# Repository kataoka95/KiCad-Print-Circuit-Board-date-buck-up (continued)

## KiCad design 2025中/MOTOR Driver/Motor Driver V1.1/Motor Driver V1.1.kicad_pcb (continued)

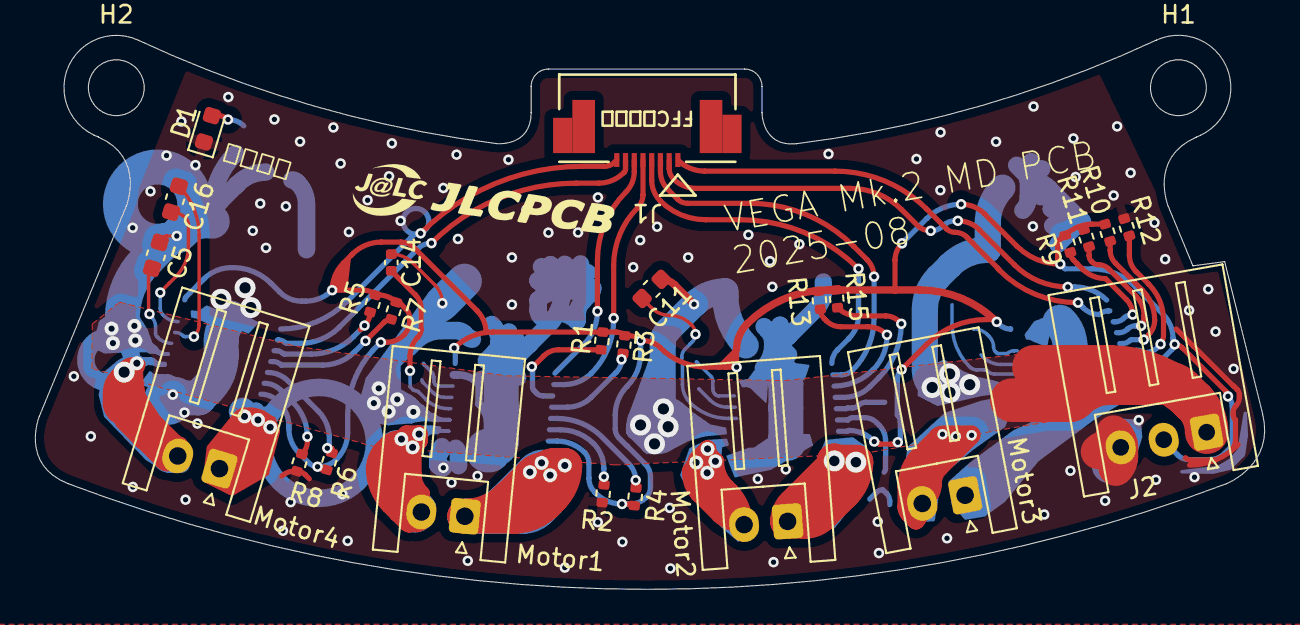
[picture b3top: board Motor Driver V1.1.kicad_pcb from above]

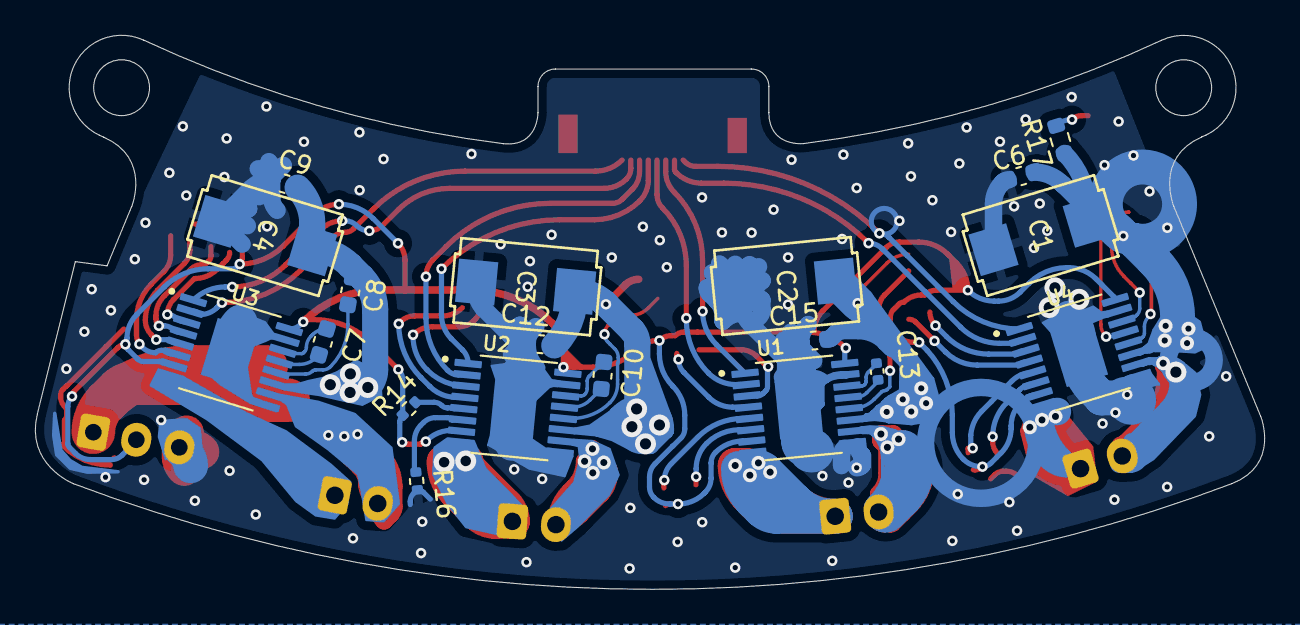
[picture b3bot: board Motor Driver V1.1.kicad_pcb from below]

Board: 2 copper layers, 70.4 x 31.7 mm, 46 parts (19 on the bottom side), 48 nets.

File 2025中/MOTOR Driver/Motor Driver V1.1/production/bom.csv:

Designator,Footprint,Quantity,Value,LCSC Part #
"C1, C2, C3, C4",293D157X9016D2TE3,4,150uF,
"C10, C16, C7",0603,3,22nF,
"C11, C12, C15, C5, C6, C8, C9",0603,7,0.1uF,
C13,0402,1,22nF,
C14,0402,1,0.1uF,
D1,0603,1,LED,
J1,FFC conector 0.5mm Pich,1,Conn_01x08_Pin,
J2,JST_XH_S3B-XH-A_1x03_P2.50mm_Horizontal,1,Conn_01x03_Pin,
"MOTOR1, MOTOR2, MOTOR3, MOTOR4",JST_XH_S2B-XH-A_1x02_P2.50mm_Horizontal,4,Conn_01x02_Pin,
"R1, R10, R11, R13, R14, R15, R3, R4, R5, R6, R7, R9",0402,12,10k,
"R12, R16, R2, R8",0402,4,2.49k,
R17,0603,1,150,
"U1, U2, U3, U4",DRV8874 IC,4,DRV8874PWPR,

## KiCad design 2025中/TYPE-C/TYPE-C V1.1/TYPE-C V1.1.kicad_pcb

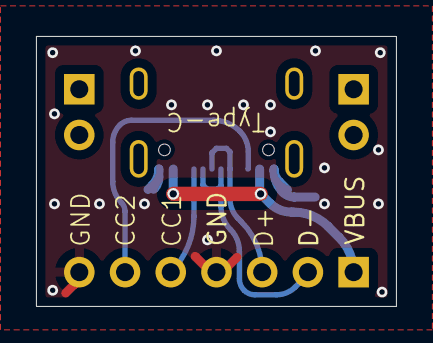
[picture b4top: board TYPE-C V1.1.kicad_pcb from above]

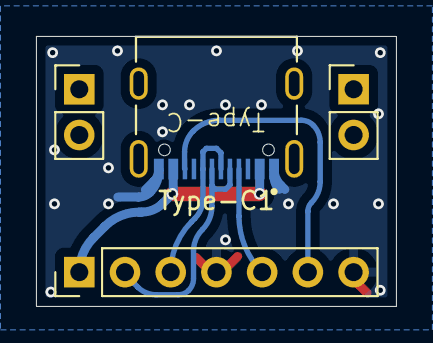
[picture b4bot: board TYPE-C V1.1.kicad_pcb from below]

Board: 2 copper layers, 20.0 x 15.0 mm, 4 parts (4 on the bottom side), 6 nets.

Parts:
J1: Conn_01x07_Pin; PinHeader_1x07_P2.54mm_Vertical
J2, J3: Conn_01x02_Pin; PinHeader_1x02_P2.54mm_Vertical
Type-C1: 5077CR-16SMC2-BK-TR; NELTRON_5077CR-16SMC2-BK-TR

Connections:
CC1: J1.5, Type-C1.A5 (CC1)
CC2: J1.6, Type-C1.B5 (CC2)
D+: J1.3, Type-C1.A6 (DP1), Type-C1.B6 (DP2)
D-: J1.2, Type-C1.A7 (DN1), Type-C1.B7 (DN2)
GND: J1.4, J1.7, Type-C1.A1_B12 (GND), Type-C1.B1_A12 (GND)
VBUS: J1.1, Type-C1.A4_B9 (VBUS), Type-C1.B4_A9 (VBUS)

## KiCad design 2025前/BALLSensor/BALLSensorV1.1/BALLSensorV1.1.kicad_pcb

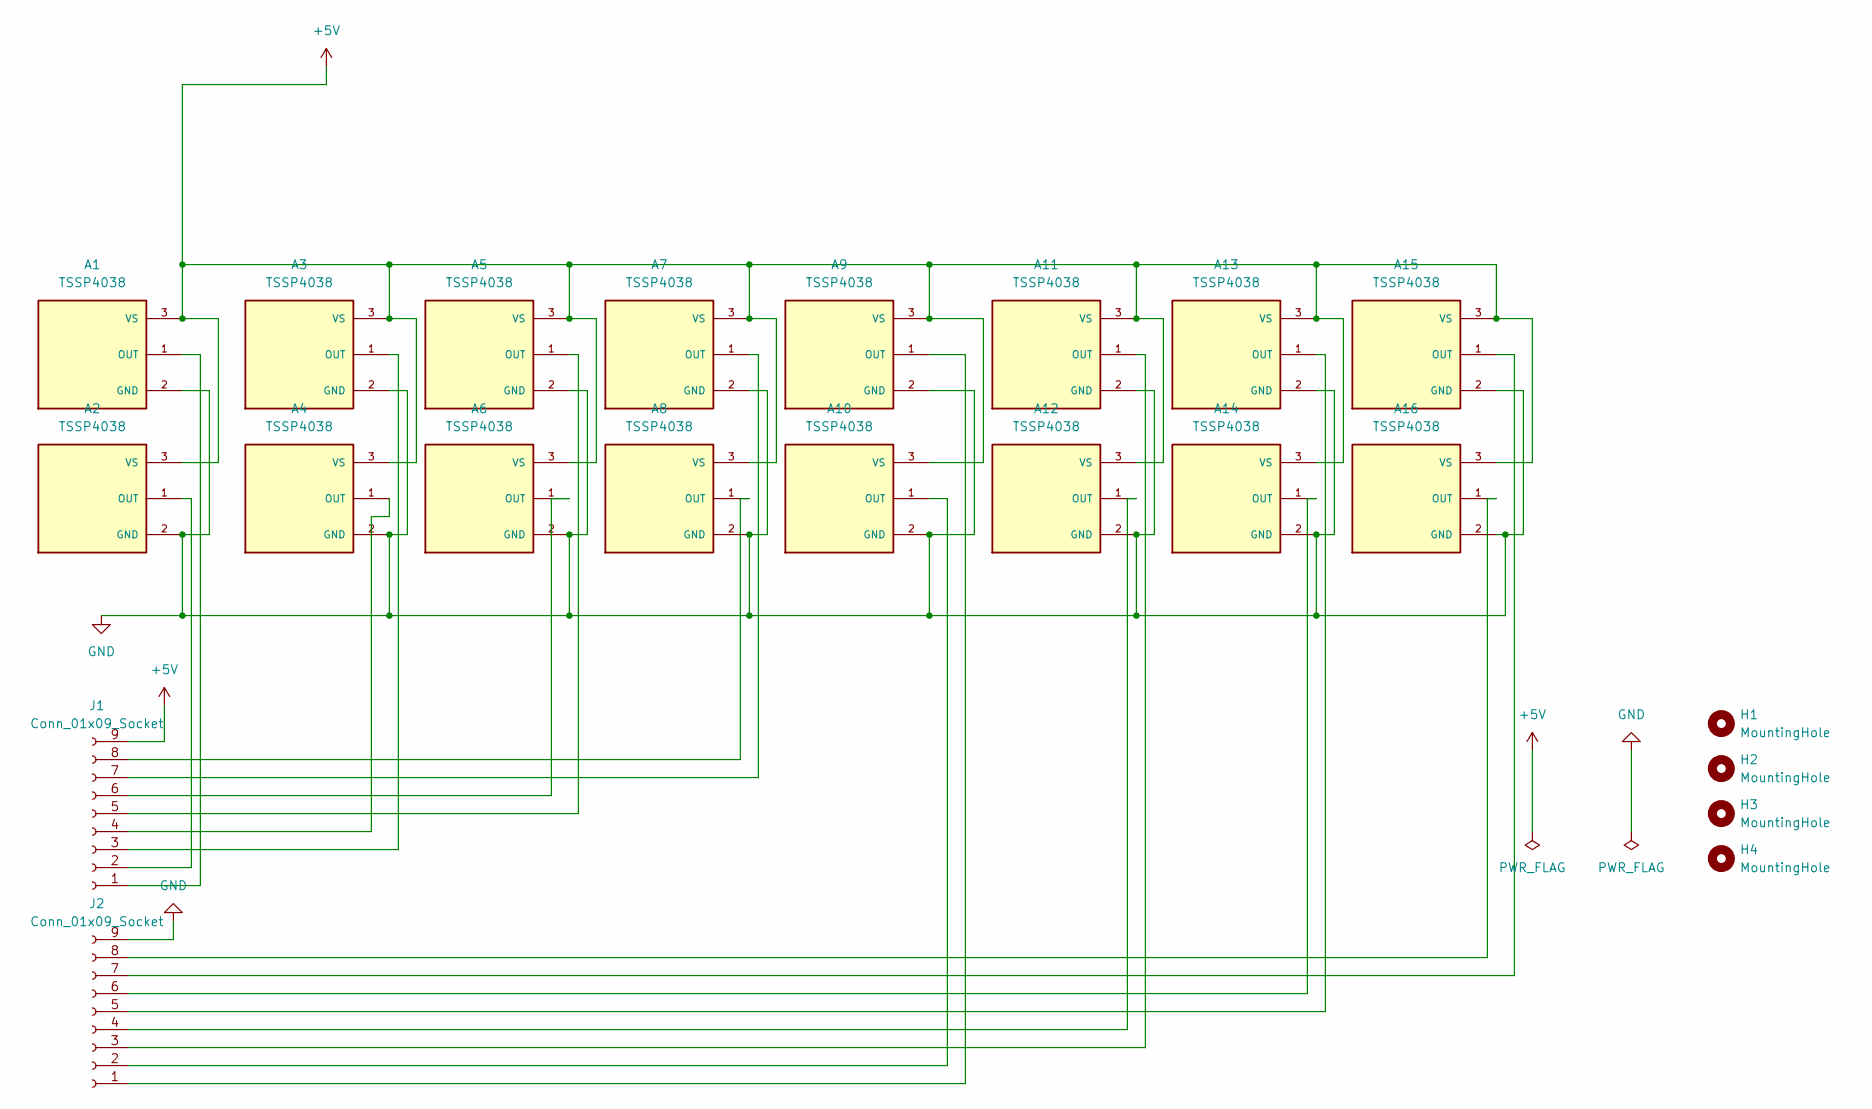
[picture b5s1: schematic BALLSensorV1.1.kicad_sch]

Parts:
A1, A2, A3, A4, A5, A6, A7, A8, A9, A10, A11, A12, A13, A14, A15, A16: TSSP4038; PARTREV 2.3
H1, H2, H3, H4: MountingHole; MountingHole_3.2mm_M3
J1, J2: Conn_01x09_Socket; JST_XH_B9B-XH-A_1x09_P2.50mm_Vertical

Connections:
+5V: A1.3 (VS), A2.3 (VS), A3.3 (VS), A4.3 (VS), A5.3 (VS), A6.3 (VS), A7.3 (VS), A8.3 (VS), A9.3 (VS), A10.3 (VS), A11.3 (VS), A12.3 (VS), A13.3 (VS), A14.3 (VS), A15.3 (VS), A16.3 (VS), J1.9
GND: A1.2 (GND), A2.2 (GND), A3.2 (GND), A4.2 (GND), A5.2 (GND), A6.2 (GND), A7.2 (GND), A8.2 (GND), A9.2 (GND), A10.2 (GND), A11.2 (GND), A12.2 (GND), A13.2 (GND), A14.2 (GND), A15.2 (GND), A16.2 (GND), J2.9
unnamed: A1.1 (OUT), J1.1
unnamed: A2.1 (OUT), J1.2
unnamed: A3.1 (OUT), J1.3
unnamed: A4.1 (OUT), J1.4
unnamed: A5.1 (OUT), J1.5
unnamed: A6.1 (OUT), J1.6
unnamed: A7.1 (OUT), J1.7
unnamed: A8.1 (OUT), J1.8
unnamed: A9.1 (OUT), J2.1
unnamed: A10.1 (OUT), J2.2
unnamed: A11.1 (OUT), J2.3
unnamed: A12.1 (OUT), J2.4
unnamed: A13.1 (OUT), J2.5
unnamed: A14.1 (OUT), J2.6
unnamed: A15.1 (OUT), J2.7
unnamed: A16.1 (OUT), J2.8

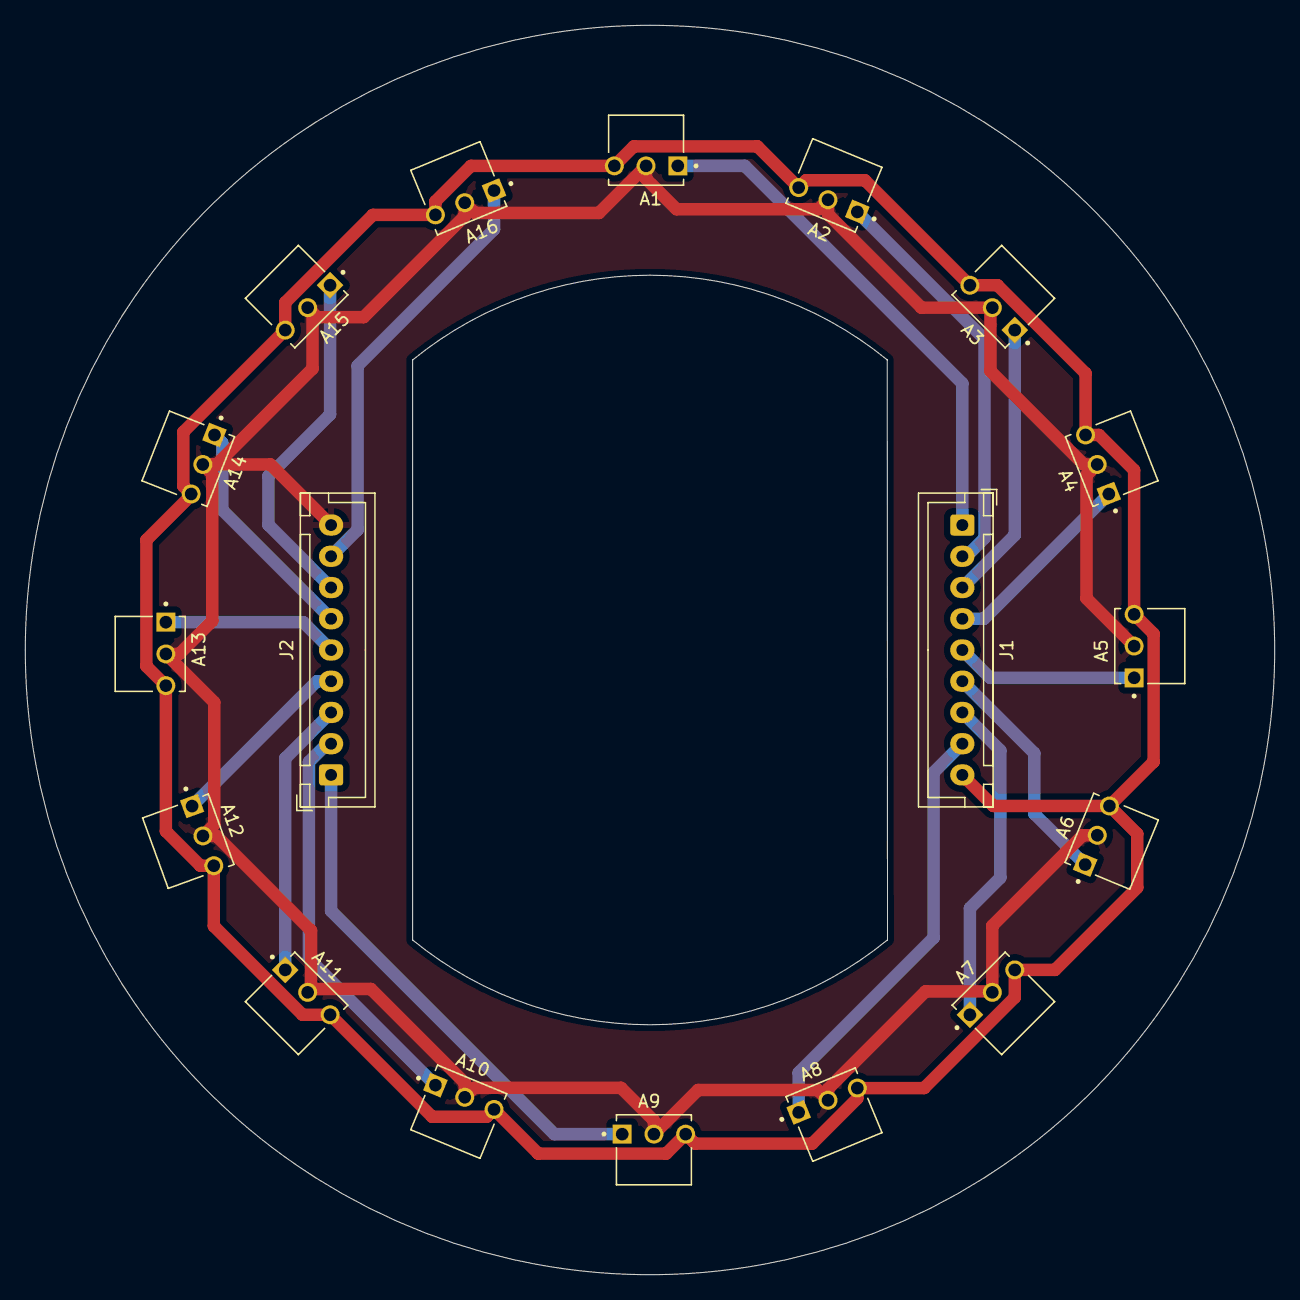
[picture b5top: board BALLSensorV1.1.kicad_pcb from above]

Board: 2 copper layers, 100.0 x 100.0 mm, 22 parts (0 on the bottom side), 18 nets.

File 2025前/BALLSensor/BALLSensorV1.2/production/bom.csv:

Designator,Footprint,Quantity,Value,LCSC Part #
"A1, A10, A11, A12, A13, A14, A15, A16, A2, A3, A4, A5, A6, A7, A8, A9",TSSP4038,16,TSSP4038,
"J1, J2",PinHeader_1x09_P2.54mm_Vertical,2,Conn_01x09_Socket,
